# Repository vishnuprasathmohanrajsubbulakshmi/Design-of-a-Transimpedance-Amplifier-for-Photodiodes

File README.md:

# Design of a Transimpedance Amplifier (TIA) for Photodiodes

## Overview
This project presents the **design, simulation, and PCB layout** of a high-sensitivity Transimpedance Amplifier (TIA) optimized for use with photodiodes.  
Two photodiode models were evaluated: **BPW 21** and **SFH 229**, with a focus on DC performance, frequency response, and noise characteristics.

---

## Objective
The primary goal was to design a low-noise, high-gain transimpedance amplifier capable of accurately converting photodiode current into a measurable voltage signal, suitable for optical sensing applications.

---

## Photodiodes Used
- **BPW 21** – High responsivity photodiode
- **SFH 229** – Silicon photodiode with low capacitance

---

## Circuit Design
- **Topology:** Op-amp based TIA
- **Feedback Resistors:** Tested at **5 MΩ** and **50 MΩ**
- **Simulation Tools:** Pspice and AutoDesk Eagle
- **PCB Layout:** Designed for low parasitics and minimal noise pickup

---

## Simulation & Analysis Results

### DC Sweep
- BPW 21 and SFH 229 tested with **R1 = 5 MΩ**
- Output voltage shows expected linear relationship with photodiode current

### AC Sweep (Frequency Response)
- Frequency response measured for both photodiodes
- Performance optimized for target bandwidth

### Noise Analysis
- **Integrated Noise:**
  - BPW 21: 36.6 µV
  - SFH 229: 4.1 µV
- **Peak-to-Peak Noise (50 MΩ feedback):**
  - BPW 21: 34.54 mV (Effective Noise: 5.76 mV)
  - SFH 229: 7.36 mV (Effective Noise: 1.23 mV)

### Offset Measurements
- BPW 21: −1.228 mV
- SFH 229: −524 µV

---

## PCB Design
- Compact, low-noise PCB layout
- Photodiode mounted close to TIA input to minimize parasitic capacitance
- Ground plane used for shielding

---

## Key Learnings
- Feedback resistor value directly impacts gain and noise
- Photodiode capacitance strongly influences bandwidth
- Layout and grounding are critical for low-noise operation

---

## Future Improvements
- Use of ultra-low bias current op-amps for further noise reduction
- Temperature drift compensation
- Integration with ADC for digital readout

---

## License

---

## How to Use
1. Clone this repository:
   ```bash
   git clone https://github.com/username/TIA-photodiode.git

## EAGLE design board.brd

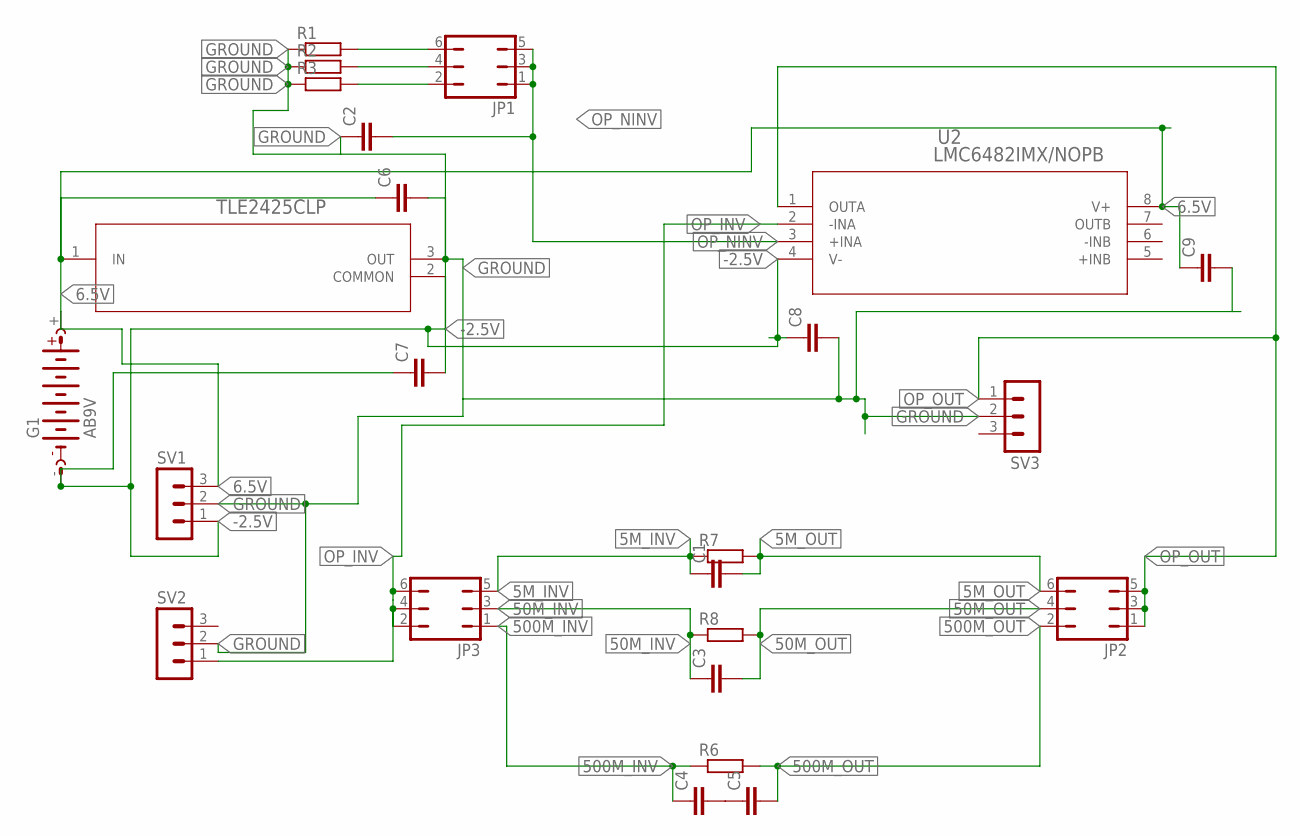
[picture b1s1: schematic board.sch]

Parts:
C1, C6, C7, C8, C9: C-EUC0402; C0402
C2, C5: C-EUC0805; C0805
C3, C4: C-EUC0603; C0603
G1: AB9V
JP1, JP2, JP3: JP3Q
R1, R6: R-EU_R2010; R2010
R2, R8: R-EU_R1206; R1206
R3, R7: R-EU_R2512; R2512
SV1, SV2, SV3: MA03-1
U1: TLE2425CLP; LP3
U2: LMC6482IMX/NOPB; M08A

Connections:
5M_INV: C1.1, JP3.5, R7.1
5M_OUT: C1.2, JP2.6, R7.2
6.5V: C6.1, C9.1, G1.+, SV1.3, U1.1 (IN), U2.8 (V+)
50M_INV: C3.1, JP3.3, R8.1
50M_OUT: C3.2, JP2.4, R8.2
500M_INV: C4.1, JP3.1, R6.1
500M_OUT: C5.2, JP2.2, R6.2
-2.5V: C7.1, C8.1, G1.-, SV1.1, U1.2 (COMMON), U2.4 (V-)
GROUND: C2.1, C6.2, C7.2, C8.2, C9.2, R1.1, R2.1, R3.1, SV1.2, SV2.2, SV3.2, U1.3 (OUT)
unnamed: C4.2, C5.1
unnamed: JP1.2, R3.2
unnamed: JP1.4, R2.2
unnamed: JP1.6, R1.2
OP_INV: JP3.2, JP3.4, JP3.6, SV2.1, U2.2 (-INA)
OP_NINV: C2.2, JP1.1, JP1.3, JP1.5, U2.3 (+INA)
OP_OUT: JP2.1, JP2.3, JP2.5, SV3.1, U2.1 (OUTA)

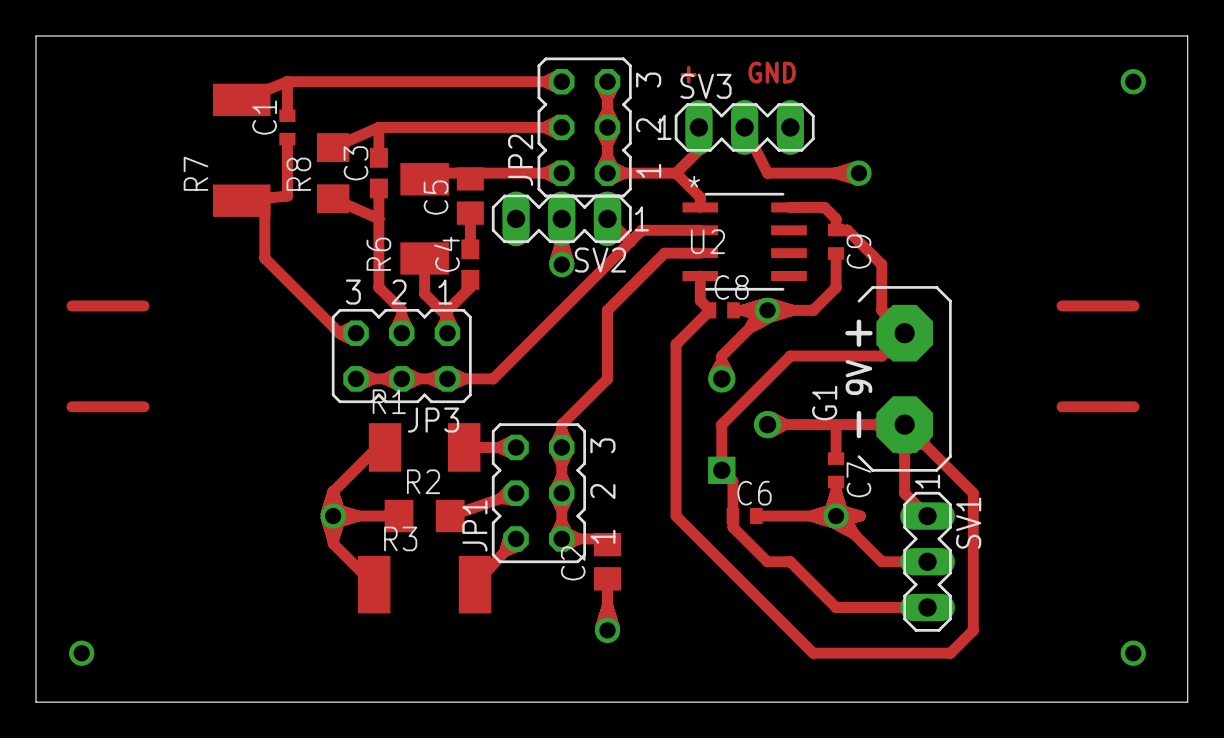
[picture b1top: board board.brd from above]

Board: 2 copper layers, 64.0 x 37.0 mm, 24 parts (1 on the bottom side), 16 nets.

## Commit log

2025-11-12 Update simulation tools in README
2025-11-12 Revise license section in README
    Updated license section to prompt for appropriate license choice.
